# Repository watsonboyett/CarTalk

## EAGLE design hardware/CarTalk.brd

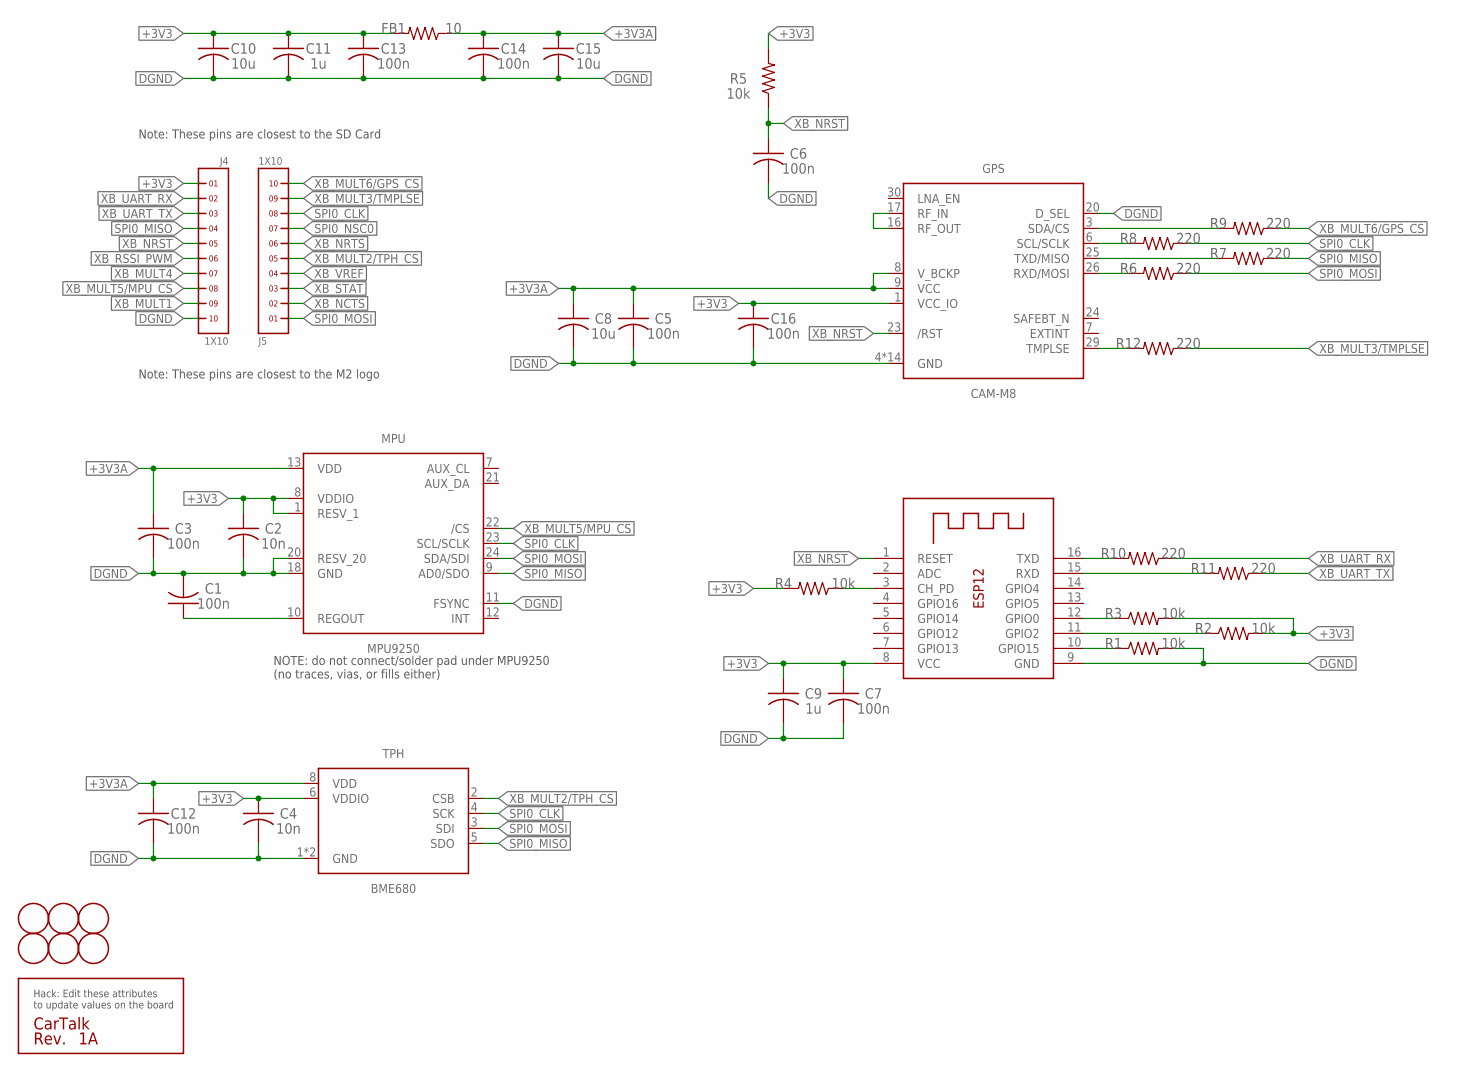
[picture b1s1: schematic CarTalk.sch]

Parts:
C1, C3, C5, C6, C7, C12, C13, C14, C16: 100n; C0603
C2, C4: 10n; C0603
C8, C10, C15: 10u; C0805
C9, C11: 1u; C0603
FB1: 10; R0603
GPS: CAM-M8
J4, J5: 1X10
MPU: MPU9250; QFN24-NP
R1, R2, R3, R4, R5: 10k; R0603
R6, R7, R8, R9, R10, R11, R12: 220; R0603
TPH: BME680; BME-DFN8
U$5: SILK_QC
U$6, U$7, U$8, U$9, U$10, U$11: FIDUCIAL; FIDUCIAL_1MM
WIFI: ESP-12

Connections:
+3V3: C2.1, C4.1, C7.1, C9.1, C10.1, C11.1, C13.1, C16.1, FB1.2, GPS.1 (VCC_IO), J4.1, MPU.1 (RESV_1), MPU.8 (VDDIO), R1.2, R2.2, R4.2, R5.2, TPH.6 (VDDIO), WIFI.8 (VCC)
+3V3A: C3.1, C5.1, C8.1, C12.1, C14.1, C15.1, FB1.1, GPS.8 (V_BCKP), GPS.9 (VCC), MPU.13 (VDD), TPH.8 (VDD)
DGND: C1.2, C2.2, C3.2, C4.2, C5.2, C6.2, C7.2, C8.2, C9.2, C10.2, C11.2, C12.2, C13.2, C14.2, C15.2, C16.2, GPS.4 (GND), GPS.5 (GND), GPS.10 (GND), GPS.11 (GND), GPS.12 (GND), GPS.13 (GND), GPS.14 (GND), GPS.15 (GND), GPS.18 (GND), GPS.19 (GND), GPS.20 (D_SEL), GPS.21 (GND), GPS.22 (GND), GPS.27 (GND), GPS.31 (GND), J4.10, MPU.11 (FSYNC), MPU.18 (GND), MPU.20 (RESV_20), R3.2, TPH.1 (GND), TPH.7 (GND), WIFI.9 (GND)
unnamed: C1.1, MPU.10 (REGOUT)
unnamed: R1.1, WIFI.12 (GPIO0)
unnamed: R2.1, WIFI.11 (GPIO2)
unnamed: R3.1, WIFI.10 (GPIO15)
unnamed: R4.1, WIFI.3 (CH_PD)
unnamed: GPS.26 (RXD/MOSI), R6.2
unnamed: GPS.25 (TXD/MISO), R7.2
unnamed: GPS.6 (SCL/SCLK), R8.2
unnamed: GPS.3 (SDA/CS), R9.2
unnamed: GPS.16 (RF_OUT), GPS.17 (RF_IN)
unnamed: R10.2, WIFI.16 (TXD)
unnamed: R11.2, WIFI.15 (RXD)
unnamed: GPS.29 (TMPLSE), R12.2
SPI0_CLK: J5.8, MPU.23 (SCL/SCLK), R8.1, TPH.4 (SCK)
SPI0_MISO: J4.4, MPU.9 (AD0/SDO), R7.1, TPH.5 (SDO)
SPI0_MOSI: J5.1, MPU.24 (SDA/SDI), R6.1, TPH.3 (SDI)
SPI0_NSC0: J5.7
XB_MULT1: J4.9
XB_MULT2/TPH_CS: J5.5, TPH.2 (CSB)
XB_MULT3/TMPLSE: J5.9, R12.1
XB_MULT4: J4.7
XB_MULT5/MPU_CS: J4.8, MPU.22 (/CS)
XB_MULT6/GPS_CS: J5.10, R9.1
XB_NCTS: J5.2
XB_NRST: C6.1, GPS.23 (/RST), J4.5, R5.1, WIFI.1 (RESET)
XB_NRTS: J5.6
XB_RSSI_PWM: J4.6
XB_STAT: J5.3
XB_UART_RX: J4.2, R10.1
XB_UART_TX: J4.3, R11.1
XB_VREF: J5.4

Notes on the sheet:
Note: These pins are closest to the SD Card
Note: These pins are closest to the M2 logo
NOTE: do not connect/solder pad under MPU9250 (no traces, vias, or fills either)

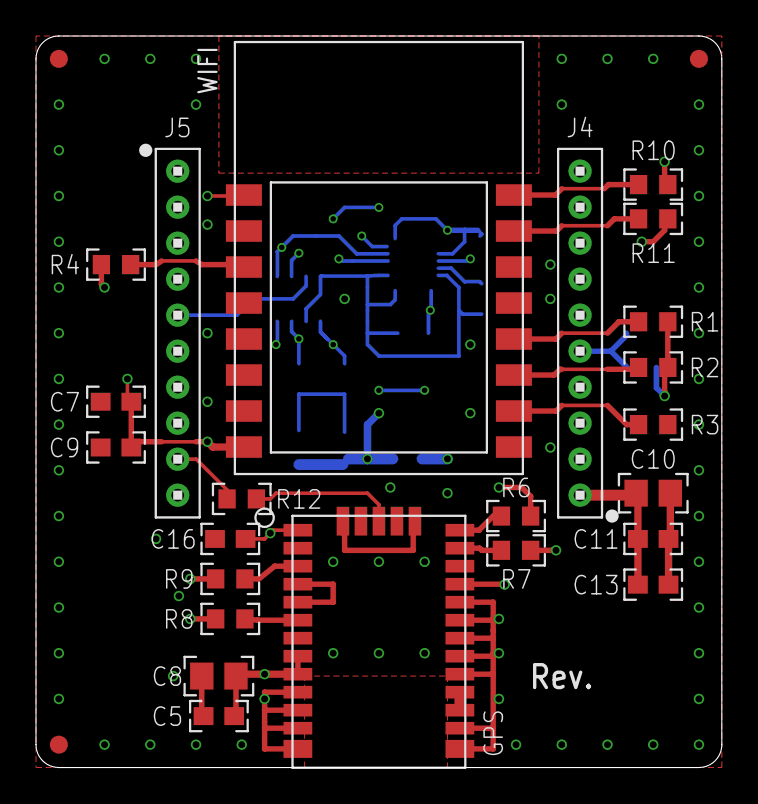
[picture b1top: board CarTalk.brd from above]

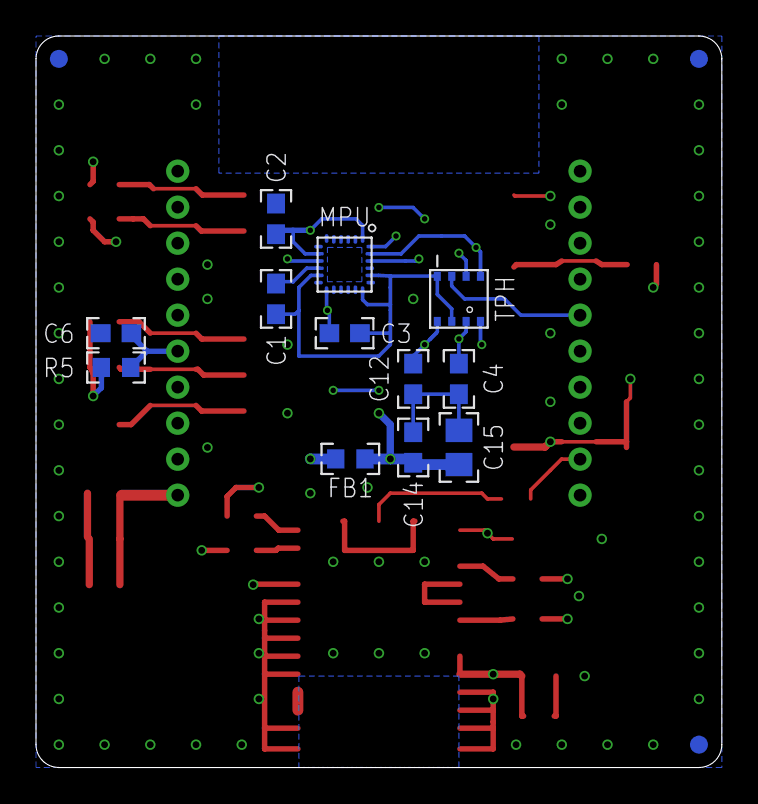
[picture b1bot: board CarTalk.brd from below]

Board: 4 copper layers, 38.1 x 40.6 mm, 42 parts (15 on the bottom side), 26 nets.

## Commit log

2017-07-06 Added initial PCB and mechanical dimensions.
2017-07-08 Finalized Rev 1A schematic and layout.
2017-07-20 Re-finalized design and layout.
2017-09-29 Simplified board layout a bit.
2017-12-25 Replaced LPS22 part with BME680 part. Upated board layout.
2017-12-25 Fixed minor layout/DFM issues
2017-12-25 Renamed files to match project name

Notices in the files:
hardware/CarTalk.sch:
CONTACT_ADDRESS: Licensed under CC-BY-SA
CONTACT_PHONE: (Creative Commons, Attribution + Share Alike)
